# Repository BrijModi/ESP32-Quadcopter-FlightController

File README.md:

# ESP32-Quadcopter-FlightController

Open-source ESP32-based flight controller for quadcopters, featuring sensor fusion, nested PID control, motor mixing, real-time Wi-Fi PID tuning, and a custom KiCad PCB with support for GPS and FPV modules.

---

## 📘 Introduction
This project is a fully custom **ESP32-based quadcopter flight controller**, built from scratch to provide complete hardware and firmware flexibility.  
Unlike commercial closed-source flight controllers, this system allows direct modification of IMU handling, PID algorithms, motor mixing, and communication layers—making it ideal for learning, research, and UAV experimentation.

The controller runs an **83 Hz control loop**, uses a **complementary filter** for real-time roll/pitch estimation, and stabilizes the quadcopter using **nested PID loops** (Angle + Rate).  
A built-in **Wi-Fi interface** enables on-the-fly PID tuning and telemetry, eliminating the need to reflash firmware between adjustments.

This repository includes the complete firmware, custom KiCad PCB design, calibration and testing utilities, project media, and a comprehensive technical report documenting the system design and implementation.

---

## ⭐ Highlights
- Custom ESP32-based flight controller firmware  
- Complementary filter for attitude estimation  
- Dual-loop PID control for roll, pitch, and yaw  
- Motor mixing for X-configuration quadcopters  
- Real-time Wi-Fi tuning dashboard  
- Custom two-layer PCB with expansion support  
- Stable and tested flight performance (90–95%)  
- Open-source and fully modifiable

---

## 🖼 Drone Image

---

## 🔧 Features
- Real-time IMU data acquisition using MPU6050  
- Complementary filter–based angle estimation  
- Nested PID loops for angle and rate stabilization  
- PWM signal generation for ESCs  
- i-BUS / PWM receiver input handling  
- Wi-Fi HTTP server for dashboard + tuning  
- Support for barometer (alt-hold), GPS, and FPV modules  
- Modular code structure for easy experimentation

---

## 🛠 Hardware Used
- ESP32 DevKit V1
- MPU6050 IMU  
- RS-2212 920KV motors + 30A ESCs  
- FlySky FS-i4X receiver  
- 3S Li-Po battery  
- F450 frame  
- Custom-designed flight controller PCB

---

## 📂 Repository Contents

- `Firmware/`
  - `Main_Firmware/` – Main ESP32-based quadcopter flight controller firmware
  - `Testing_Calibration/` – Calibration, testing, and Wi-Fi PID tuning utilities
  
- `Hardware/`
  - `Drone Flight Controller/` – Complete KiCad project (schematic, PCB layout, and project files)
  - `FC Gerber.zip` – PCB manufacturing (Gerber) files
  - `PCB View.pdf` – PCB layout overview
  - `Schematic.pdf` – Flight controller circuit schematic
  
- `Media/`
  - `Drone/` – Drone assembly, flight controller, and hardware images
  - `Test Flight and Calibration/` – Flight test videos, calibration recordings, and PID response graph

- `Technical Report.pdf` – Comprehensive technical documentation covering hardware design, firmware architecture, implementation, and testing

---

## 💻 Software Requirements

- Arduino IDE 2.x
- ESP32 Arduino Core
- KiCad 9.x (for PCB design)

---

## 📚 Libraries Used

- `Wire` – I²C communication
- `ESP32Servo` – ESC PWM control
- `WiFi` – Wireless communication
- `AsyncTCP` – Asynchronous TCP networking
- `ESPAsyncWebServer` – Web-based PID tuning dashboard
- `SPIFFS` – Web dashboard file storage

---

## 🚀 Getting Started

Follow the steps below to configure and fly the quadcopter for the first time.

### 1. Hardware Setup
- Assemble the quadcopter and connect all hardware components.
- Wire the ESP32, MPU6050, ESCs, receiver, and motors according to the provided schematic.

### 2. Verify Receiver and ESCs
- Upload the firmware from `Firmware/Testing_Calibration/Receiver_PWM_Testing/` to verify proper receiver operation.
- Upload the firmware from `Firmware/Testing_Calibration/ESC_Calibration/` and calibrate all ESCs.

### 3. Calibrate the IMU
- Upload the firmware from `Firmware/Testing_Calibration/IMU_Calibration/`.
- Place the quadcopter on a level surface and perform the IMU calibration.
- Copy the generated accelerometer and gyroscope offset values into both the main flight controller firmware and the PID tuning firmware.

### 4. Tune the PID Controller
- Upload the firmware from `Firmware/Testing_Calibration/PID_Tuning_Webserver/`.
- Connect to the ESP32 Wi-Fi access point and open the PID tuning dashboard.
- Tune the roll, pitch, and yaw PID gains until stable flight performance is achieved.
- Copy the optimized PID values into the main flight controller firmware.

### 5. Upload the Main Flight Controller Firmware
- Open `Firmware/Main_Firmware/Flight_Controller_v2/Flight_Controller_v2.ino`.
- Update the firmware with the calibrated IMU offsets and tuned PID gains.
- Upload the firmware to the ESP32.

### 6. Perform Flight Testing
- Verify the motor rotation direction and propeller orientation.
- Perform an initial low-throttle hover test in a safe, open area.
- Fine-tune the PID gains as required to achieve stable and responsive flight.

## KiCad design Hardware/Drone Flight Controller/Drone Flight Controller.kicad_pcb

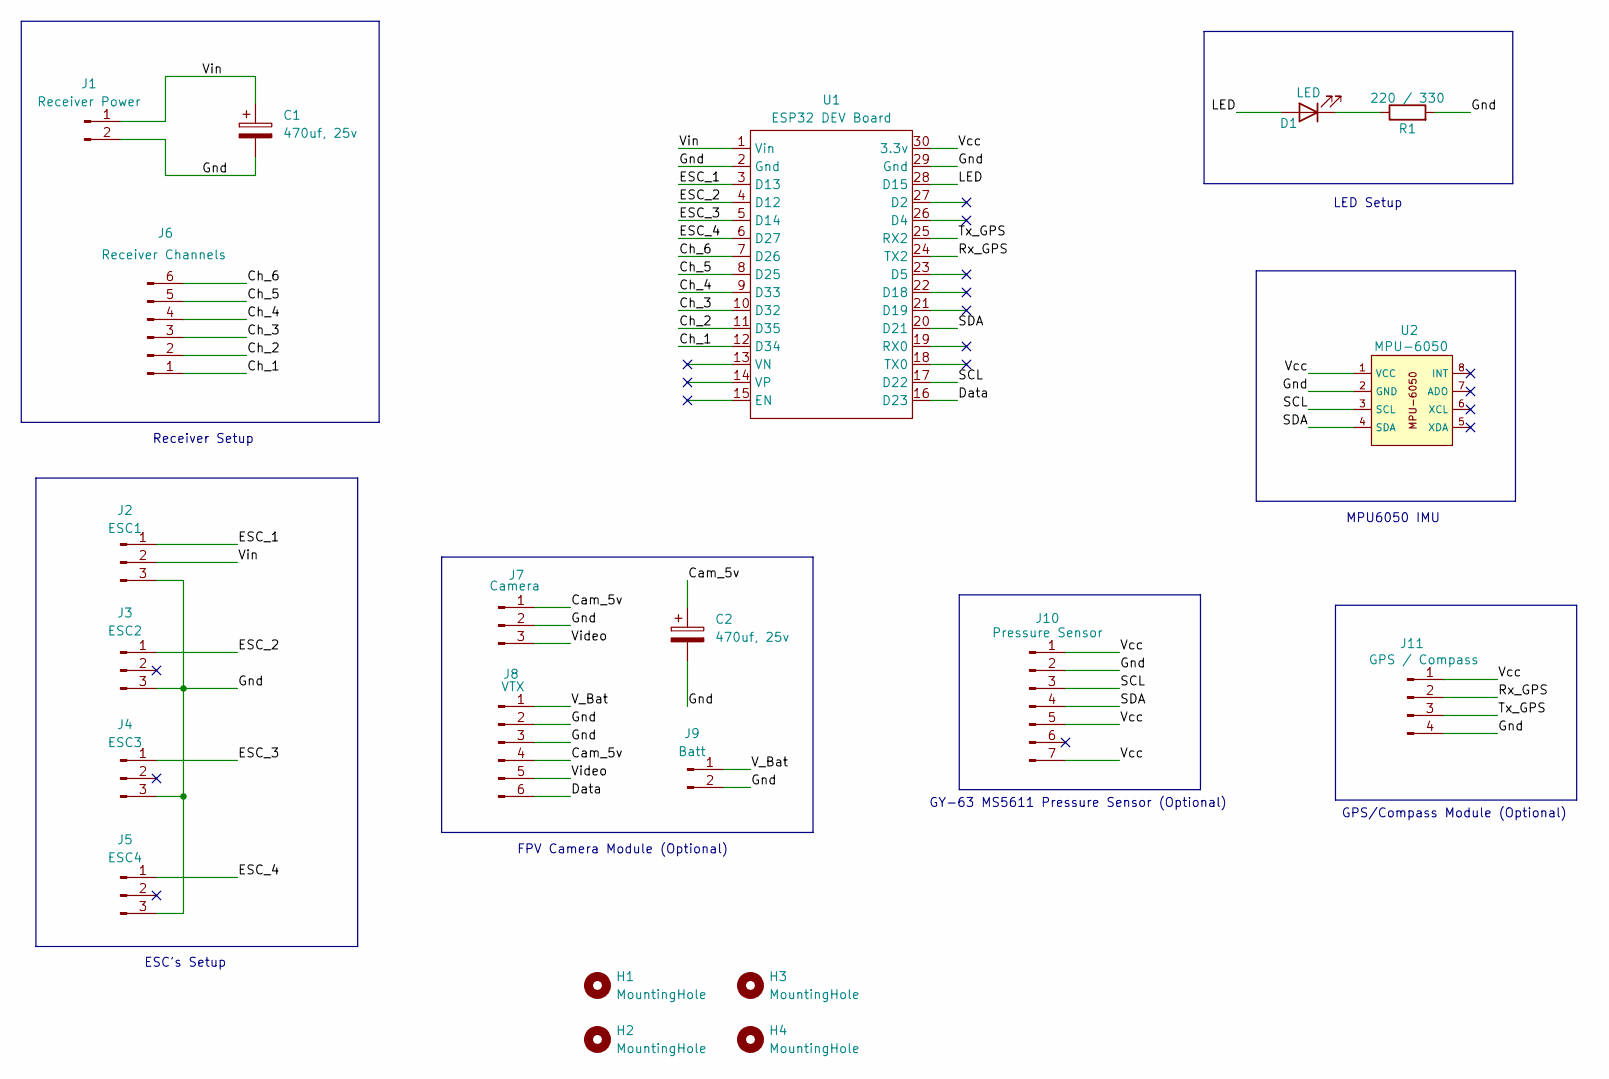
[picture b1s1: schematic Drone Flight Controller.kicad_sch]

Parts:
C1, C2: 470uf, 25v; CP_Elec_6.3x7.7
D1: LED; LED_D5.0mm
H1, H2, H3, H4: MountingHole; MountingHole_3.2mm_M3
J1: Receiver Power; PinHeader_1x02_P2.54mm_Vertical
J2: ESC1; PinHeader_1x03_P2.54mm_Vertical
J3: ESC2; PinHeader_1x03_P2.54mm_Vertical
J4: ESC3; PinHeader_1x03_P2.54mm_Vertical
J5: ESC4; PinHeader_1x03_P2.54mm_Vertical
J6: Receiver Channels; PinHeader_1x06_P2.54mm_Vertical
J7: Camera; JST_XH_S3B-XH-A_1x03_P2.50mm_Horizontal
J8: VTX; JST_GH_SM06B-GHS-TB_1x06-1MP_P1.25mm_Horizontal
J9: Batt; PinHeader_1x02_P2.54mm_Vertical
J10: Pressure Sensor; PinHeader_1x07_P2.54mm_Vertical
J11: GPS / Compass; PinHeader_1x04_P2.54mm_Vertical
R1: 220 / 330; R_Axial_DIN0207_L6.3mm_D2.5mm_P7.62mm_Horizontal
U1: ESP32 DEV Board; MODULE_ESP32_DEVKIT_V1
U2: MPU-6050; PinHeader_1x08_P2.54mm_Vertical

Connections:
/Cam_5v: C2.1, J7.1, J8.4
/Ch_1: J6.1, U1.12 (D34)
/Ch_2: J6.2, U1.11 (D35)
/Ch_3: J6.3, U1.10 (D32)
/Ch_4: J6.4, U1.9 (D33)
/Ch_5: J6.5, U1.8 (D25)
/Ch_6: J6.6, U1.7 (D26)
/Data: J8.6, U1.16 (D23)
/ESC_1: J2.1, U1.3 (D13)
/ESC_2: J3.1, U1.4 (D12)
/ESC_3: J4.1, U1.5 (D14)
/ESC_4: J5.1, U1.6 (D27)
/Gnd: C1.2, C2.2, J1.2, J2.3, J3.3, J4.3, J5.3, J7.2, J8.2, J8.3, J9.2, J10.2, J11.4, R1.2, U1.2 (Gnd), U1.29 (Gnd), U2.2 (GND)
/LED: D1.2 (A), U1.28 (D15)
/Rx_GPS: J11.2, U1.24 (TX2)
/SCL: J10.3, U1.17 (D22), U2.3 (SCL)
/SDA: J10.4, U1.20 (D21), U2.4 (SDA)
/Tx_GPS: J11.3, U1.25 (RX2)
/V_Bat: J8.1, J9.1
/Vcc: J10.1, J10.5, J10.7, J11.1, U1.30 (3.3v), U2.1 (VCC)
/Video: J7.3, J8.5
/Vin: C1.1, J1.1, J2.2, U1.1 (Vin)
unnamed: D1.1 (K), R1.1

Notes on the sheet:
MPU6050 IMU
LED Setup
FPV Camera Module (Optional)
Receiver Setup
GPS/Compass Module (Optional)
GY-63 MS5611 Pressure Sensor (Optional)
ESC's Setup

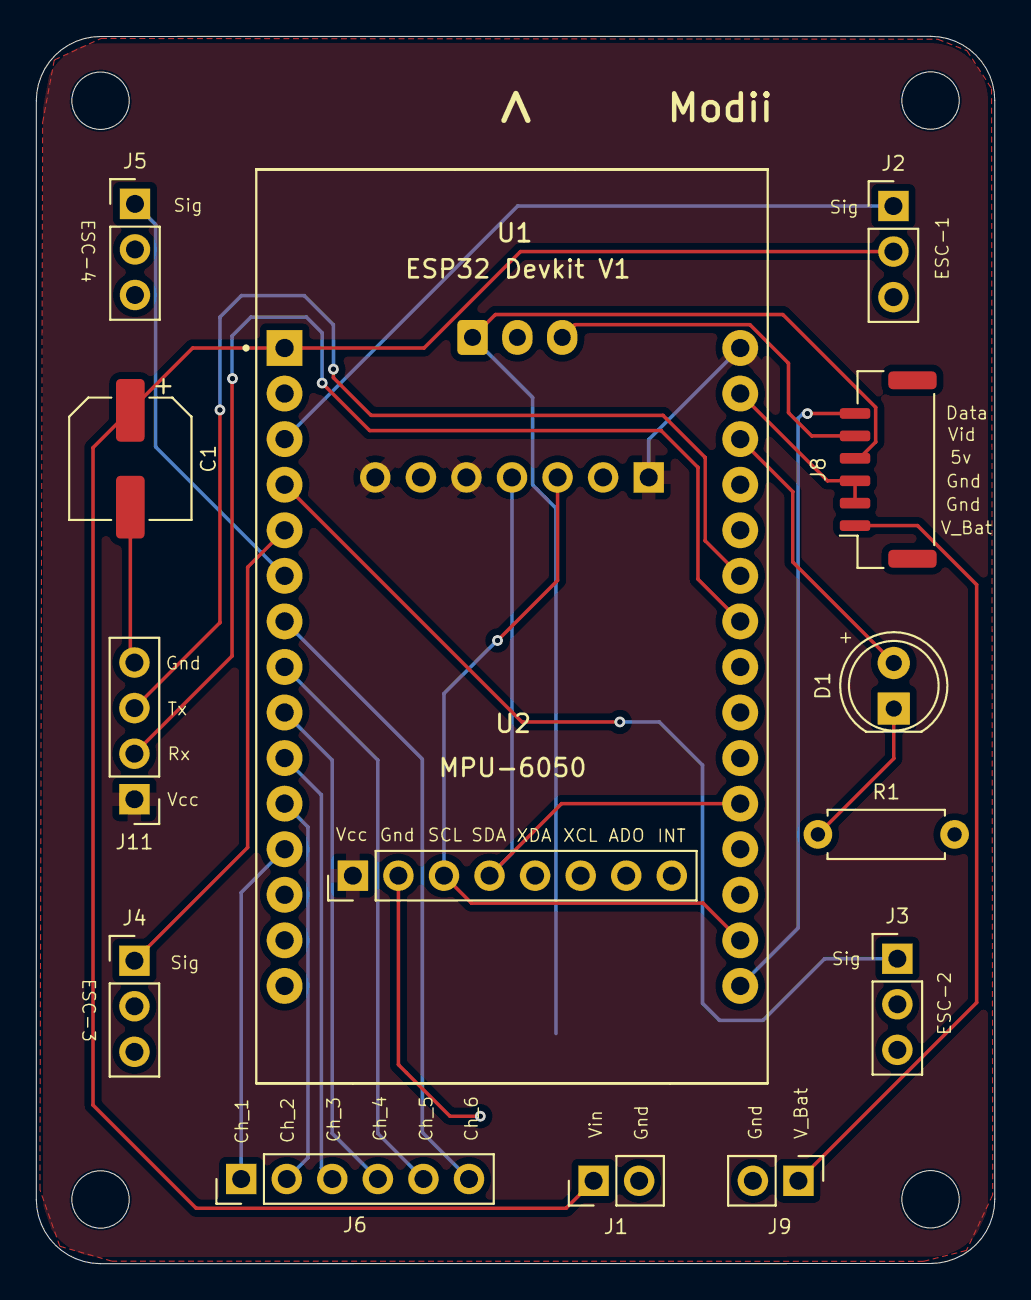
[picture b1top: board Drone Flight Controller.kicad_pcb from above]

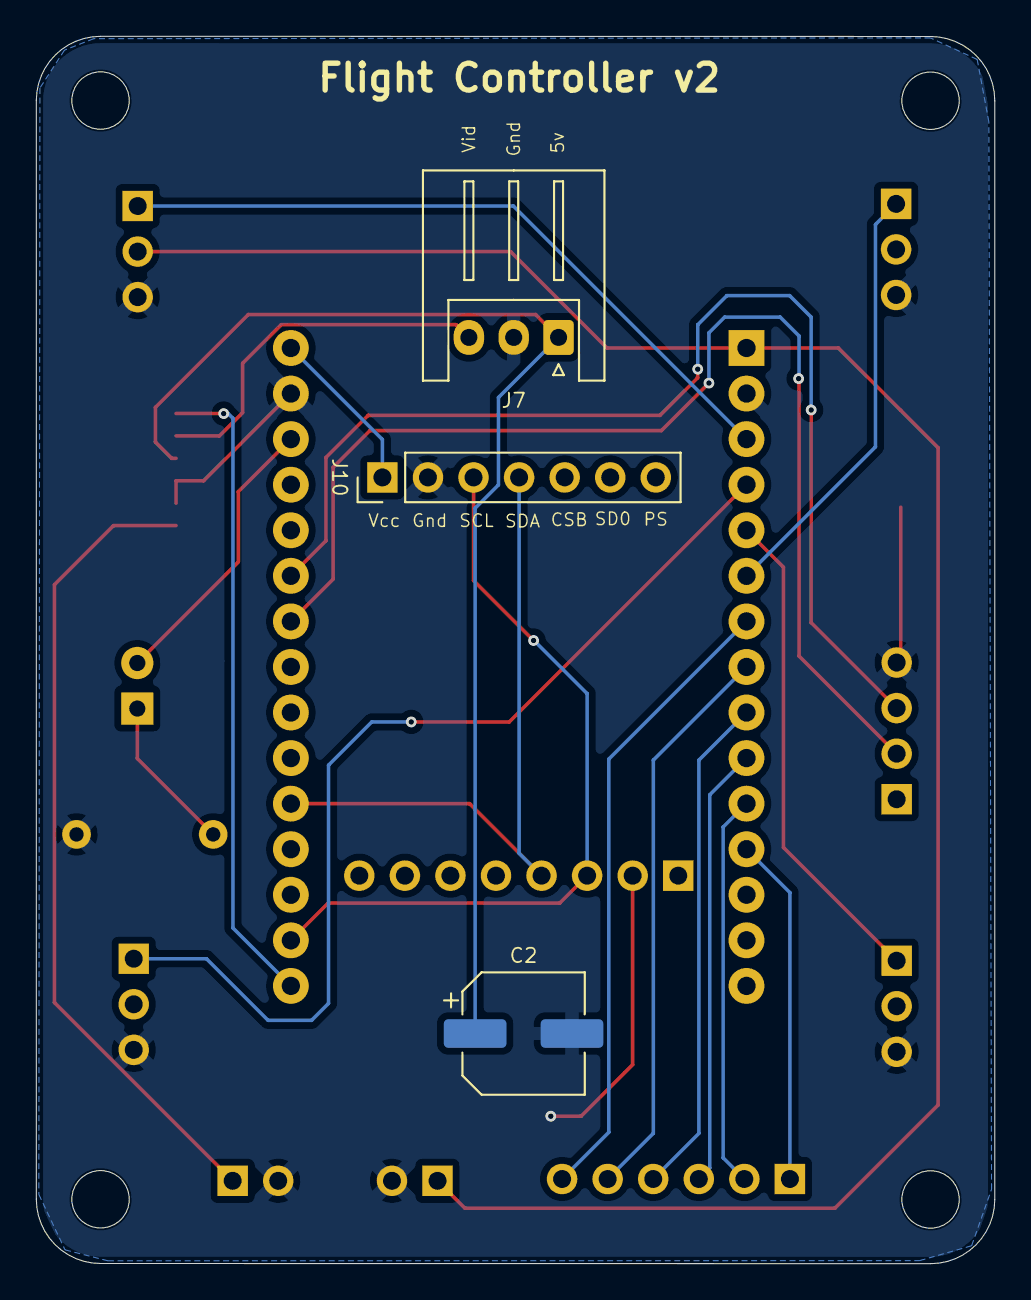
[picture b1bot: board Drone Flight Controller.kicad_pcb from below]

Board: 2 copper layers, 53.4 x 68.4 mm, 21 parts (3 on the bottom side), 23 nets.

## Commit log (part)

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2025-11-28 README.md
2025-11-28 Codes for Flight Controller
2025-11-28 Technical Report of Drone Flight Controller
2025-11-28 Flight Controller PCB Design
2025-11-28 Drone Flight Test Media
2025-11-28 Drone Test Flight (Prototyping Stage)
2025-12-11 Firmware for Flight Controller
2025-12-11 Drone Prototyping Image
2025-12-11 Drone Media
